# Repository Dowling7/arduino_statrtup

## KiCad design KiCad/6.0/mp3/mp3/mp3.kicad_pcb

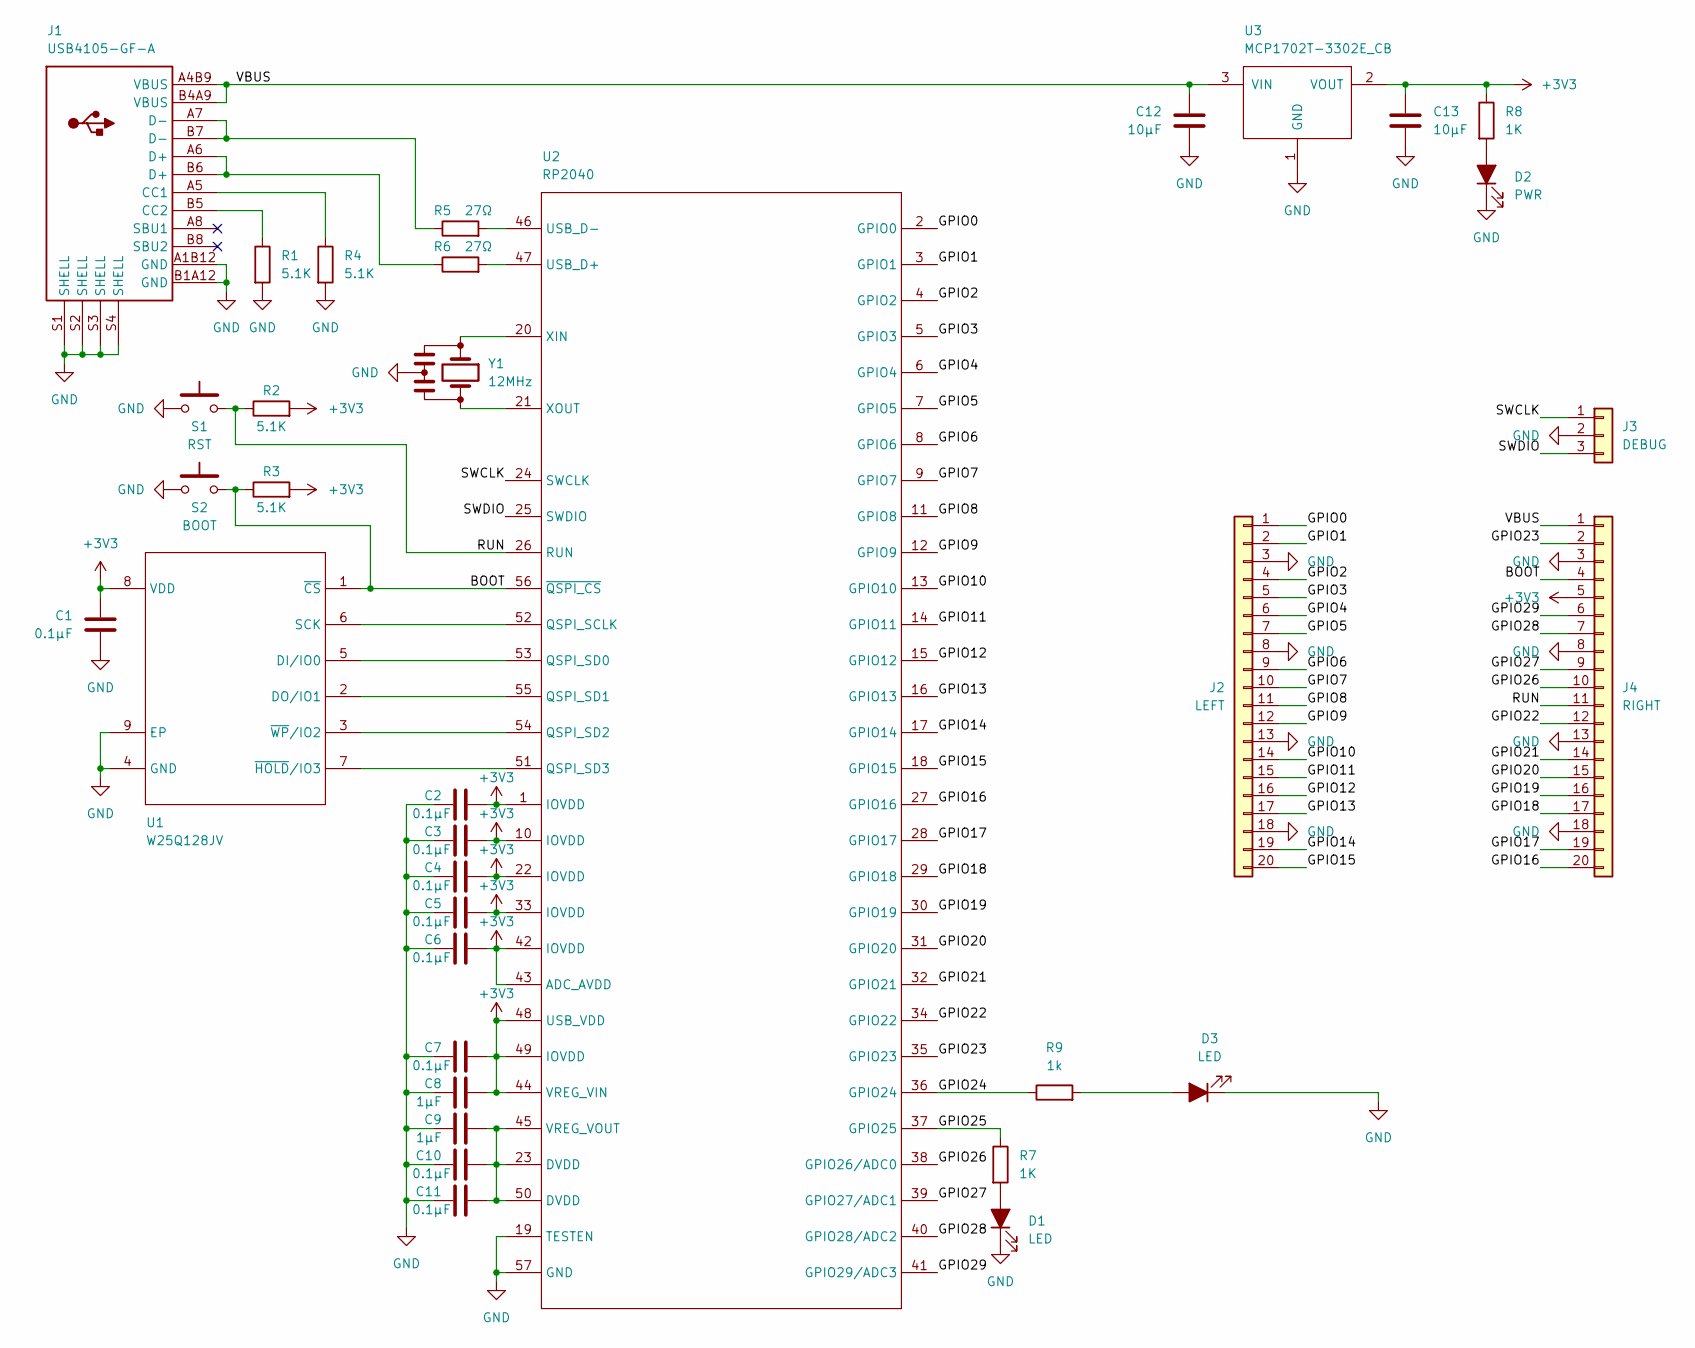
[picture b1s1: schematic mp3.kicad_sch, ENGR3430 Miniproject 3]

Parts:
C1, C2, C3, C4, C5, C6, C7, C10, C11: 0.1µF; C_0402_1005Metric
C8, C9: 1µF; C_0402_1005Metric
C12, C13: 10µF; C_0603_1608Metric
D1, D3: LED; LED_0805_2012Metric
D2: PWR; LED_0805_2012Metric
J1: USB4105-GF-A
J2: LEFT; PinSocket_1x20_P2.54mm_Vertical
J3: DEBUG; PinSocket_1x03_P1.27mm_Vertical
J4: RIGHT; PinSocket_1x20_P2.54mm_Vertical
R1, R2, R3, R4: 5.1K; R_0402_1005Metric
R5, R6: 27Ω; R_0402_1005Metric
R7, R8: 1K; R_0402_1005Metric
R9: 1k; R_0402_1005Metric
S1: RST; SW_SPST_CK_KXT3
S2: BOOT; SW_SPST_CK_KXT3
U1: W25Q128JV; MIC_WSON-8
U2: RP2040
U3: MCP1702T-3302E_CB; Microchip-MCP1702T-3302E_CB-Level_B
Y1: 12MHz; Resonator_SMD_Murata_CSTxExxV-3Pin_3.0x1.1mm

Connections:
+3V3: C1.2, C2.1, C3.1, C4.1, C5.1, C6.1, C7.1, C8.1, C13.1, J4.5, R2.2, R3.2, R8.1, U1.8 (VDD), U2.1 (IOVDD), U2.10 (IOVDD), U2.22 (IOVDD), U2.33 (IOVDD), U2.42 (IOVDD), U2.43 (ADC_AVDD), U2.44 (VREG_VIN), U2.48 (USB_VDD), U2.49 (IOVDD), U3.2 (VOUT)
/BOOT: J4.4, R3.1, S2.2, U1.1 (~CS), U2.56 (~QSPI_CS)
/GPIO0: J2.1, U2.2 (GPIO0)
/GPIO1: J2.2, U2.3 (GPIO1)
/GPIO2: J2.4, U2.4 (GPIO2)
/GPIO3: J2.5, U2.5 (GPIO3)
/GPIO4: J2.6, U2.6 (GPIO4)
/GPIO5: J2.7, U2.7 (GPIO5)
/GPIO6: J2.9, U2.8 (GPIO6)
/GPIO7: J2.10, U2.9 (GPIO7)
/GPIO8: J2.11, U2.11 (GPIO8)
/GPIO9: J2.12, U2.12 (GPIO9)
/GPIO10: J2.14, U2.13 (GPIO10)
/GPIO11: J2.15, U2.14 (GPIO11)
/GPIO12: J2.16, U2.15 (GPIO12)
/GPIO13: J2.17, U2.16 (GPIO13)
/GPIO14: J2.19, U2.17 (GPIO14)
/GPIO15: J2.20, U2.18 (GPIO15)
/GPIO16: J4.20, U2.27 (GPIO16)
/GPIO17: J4.19, U2.28 (GPIO17)
/GPIO18: J4.17, U2.29 (GPIO18)
/GPIO19: J4.16, U2.30 (GPIO19)
/GPIO20: J4.15, U2.31 (GPIO20)
/GPIO21: J4.14, U2.32 (GPIO21)
/GPIO22: J4.12, U2.34 (GPIO22)
/GPIO23: J4.2, U2.35 (GPIO23)
/GPIO24: R9.1, U2.36 (GPIO24)
/GPIO25: R7.1, U2.37 (GPIO25)
/GPIO26: J4.10, U2.38 (GPIO26/ADC0)
/GPIO27: J4.9, U2.39 (GPIO27/ADC1)
/GPIO28: J4.7, U2.40 (GPIO28/ADC2)
/GPIO29: J4.6, U2.41 (GPIO29/ADC3)
/RUN: J4.11, R2.1, S1.2, U2.26 (RUN)
/SWCLK: J3.1, U2.24 (SWCLK)
/SWDIO: J3.3, U2.25 (SWDIO)
/VBUS: C12.2, J1.A4B9 (VBUS), J1.B4A9 (VBUS), J4.1, U3.3 (VIN)
GND: C1.1, C2.2, C3.2, C4.2, C5.2, C6.2, C7.2, C8.2, C9.2, C10.2, C11.2, C12.1, C13.2, D1.1 (K), D2.1 (K), D3.1 (K), J1.A1B12 (GND), J1.B1A12 (GND), J1.S1 (SHELL), J1.S2 (SHELL), J1.S3 (SHELL), J1.S4 (SHELL), J2.3, J2.8, J2.13, J2.18, J3.2, J4.3, J4.8, J4.13, J4.18, R1.2, R4.2, S1.1, S2.1, U1.4 (GND), U1.9 (EP), U2.19 (TESTEN), U2.57 (GND), U3.1 (GND), Y1.2
unnamed: C9.1, C10.1, C11.1, U2.23 (DVDD), U2.45 (VREG_VOUT), U2.50 (DVDD)
unnamed: D1.2 (A), R7.2
unnamed: D2.2 (A), R8.2
unnamed: J1.A5 (CC1), R4.1
unnamed: J1.A6 (D+), J1.B6 (D+), R6.1
unnamed: J1.A7 (D-), J1.B7 (D-), R5.1
unnamed: J1.B5 (CC2), R1.1
unnamed: R5.2, U2.46 (USB_D-)
unnamed: R6.2, U2.47 (USB_D+)
unnamed: D3.2 (A), R9.2
unnamed: U1.2 (DO/IO1), U2.55 (QSPI_SD1)
unnamed: U1.3 (~WP/IO2), U2.54 (QSPI_SD2)
unnamed: U1.5 (DI/IO0), U2.53 (QSPI_SD0)
unnamed: U1.6 (SCK), U2.52 (QSPI_SCLK)
unnamed: U1.7 (~HOLD/IO3), U2.51 (QSPI_SD3)
unnamed: U2.20 (XIN), Y1.1
unnamed: U2.21 (XOUT), Y1.3

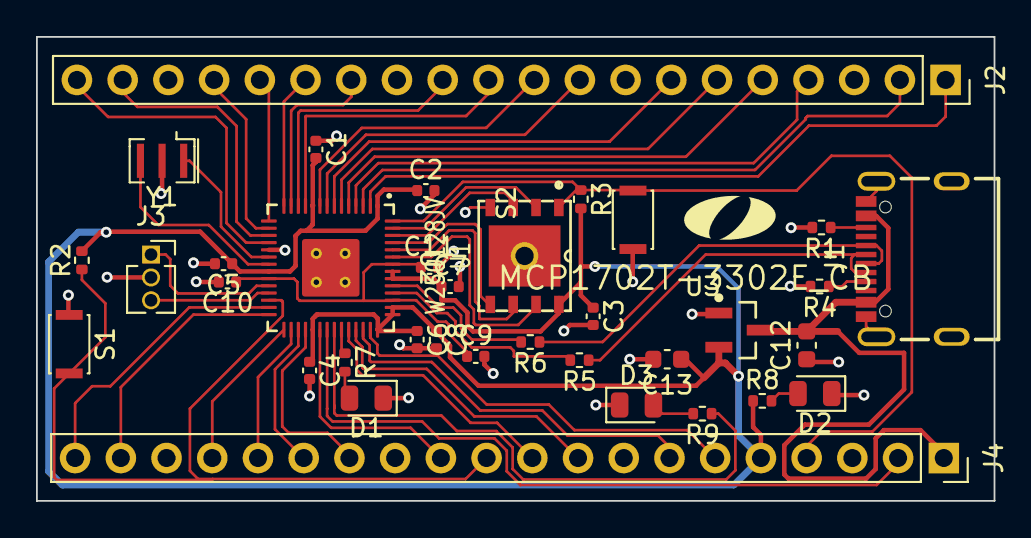
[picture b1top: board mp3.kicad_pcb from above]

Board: 2 copper layers, 53.2 x 25.8 mm, 36 parts (0 on the bottom side), 54 nets.

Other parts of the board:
OlinLogoSm: G***; OlinLogoSm

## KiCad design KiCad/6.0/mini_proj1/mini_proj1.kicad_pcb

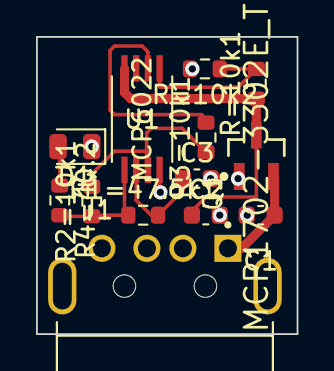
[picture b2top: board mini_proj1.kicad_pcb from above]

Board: 2 copper layers, 14.5 x 16.5 mm, 13 parts (0 on the bottom side), 9 nets.

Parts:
C1, C2, C3: C=10u; C_0603_1608Metric
D1: LED; LED_0805_2012Metric
J1: USB_A; MOLEX_48037-0001
Q1: MCP1702-3302E_TO; Microchip-MCP1702T-3302E_CB-Level_B
R1=47.5k1, R2=10k1, R3=10k1, R4=40.2: R_US; R_0603_1608Metric
R=10k1, R=10k2: R_Small_US; R_0603_1608Metric
U1: MCP6022; MCP6022T-I&slash_ST

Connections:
GND: C1.2, C2.2, C3.2, D1.1 (K), J1.4 (GND), J1.5 (Shield), Q1.1 (GND), R=10k2.2, U1.4 (V-)
unnamed: C1.1, J1.1 (VBUS), Q1.2 (VIN)
unnamed: C3.1, R1=47.5k1.2, U1.2 (-)
unnamed: D1.2 (A), R4=40.2.1
unnamed: C2.1, Q1.3 (VOUT), R=10k1.1, U1.8 (V+)
unnamed: R1=47.5k1.1, R2=10k1.1, R4=40.2.2, U1.1
unnamed: R2=10k1.2, R3=10k1.1, U1.3 (+)
unnamed: R3=10k1.2, U1.6 (-)
unnamed: R=10k1.2, R=10k2.1, U1.5 (+)

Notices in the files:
parts and their libraries:
Copyright 2021 Accelerated Designs. All rights reserved.
